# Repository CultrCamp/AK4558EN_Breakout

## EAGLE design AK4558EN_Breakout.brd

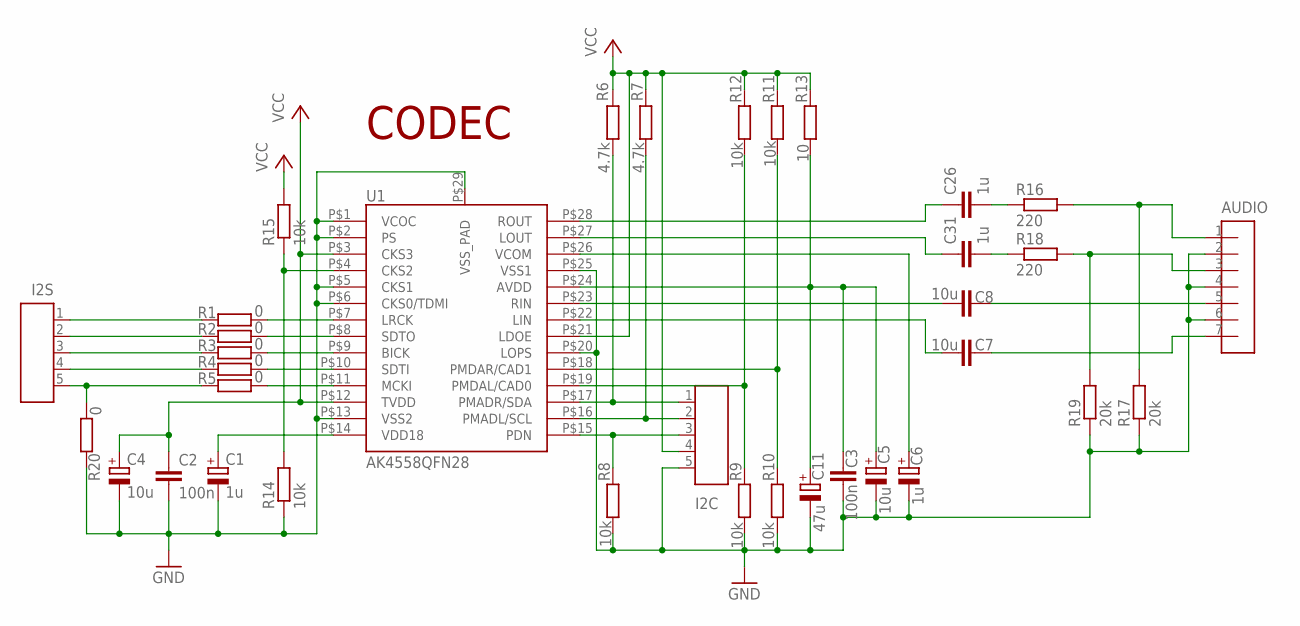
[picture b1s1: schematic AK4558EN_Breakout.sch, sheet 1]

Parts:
AUDIO: PH_ST_7; HDRV7W64P254_1X7_1016X508X838B
C1, C6: 1u; SMC_A
C2, C3: 100n; C0603
C4, C5: 10u; SMC_B
C7, C8: 10u; C0603
C11: 47u; SMC_C
C26, C31: 1u; C0603
I2C, I2S: PH_ST_5; HDRV5W64P254_1X5_1016X508X838B
R1, R2, R3, R4, R5, R20: 0; R0603
R6, R7: 4.7k; R0603
R8, R9, R10, R11, R12, R14, R15: 10k; R0603
R13: 10; R0603
R16, R18: 220; R0603
R17, R19: 20k; R0603
U1: AK4558QFN28; QFN28_5X5

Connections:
CKS2: R14.2, R15.1, U1.P$4 (CKS2)
CODEC_AVDD: C3.1, C5.+, C11.+, R13.1, U1.P$24 (AVDD)
GND: AUDIO.2, AUDIO.4, AUDIO.6, C1.-, C2.2, C3.2, C4.-, C5.-, C6.-, C11.-, I2C.5, R8.1, R9.1, R10.1, R14.1, R17.1, R19.1, R20.1, U1.P$1 (VCOC), U1.P$2 (PS), U1.P$5 (CKS1), U1.P$6 (CKS0/TDMI), U1.P$13 (VSS2), U1.P$20 (LOPS), U1.P$25 (VSS1), U1.P$29 (VSS_PAD)
LIN: AUDIO.7, C7.1
LOUT: AUDIO.3, R18.2, R19.2
MCLK: I2S.5, R5.1, R20.2
unnamed: I2S.4, R4.1
unnamed: C7.2, U1.P$22 (LIN)
unnamed: C26.2, R16.1
unnamed: C6.+, U1.P$26 (VCOM)
unnamed: R5.2, U1.P$11 (MCKI)
unnamed: C8.2, U1.P$23 (RIN)
unnamed: C31.1, U1.P$27 (LOUT)
unnamed: C31.2, R18.1
unnamed: C26.1, U1.P$28 (ROUT)
unnamed: R10.2, R11.1, U1.P$18 (PMDAR/CAD1)
unnamed: R9.2, R12.1, U1.P$19 (PMDAL/CAD0)
unnamed: I2S.3, R3.1
unnamed: I2S.2, R2.1
unnamed: I2S.1, R1.1
unnamed: C1.+, U1.P$14 (VDD18)
unnamed: R1.2, U1.P$7 (LRCK)
unnamed: R2.2, U1.P$8 (SDTO)
unnamed: R3.2, U1.P$9 (BICK)
unnamed: R4.2, U1.P$10 (SDTI)
PDN: I2C.3, R8.2, U1.P$15 (PDN)
RIN: AUDIO.5, C8.1
ROUT: AUDIO.1, R16.2, R17.2
SCL: I2C.2, R7.1, U1.P$16 (PMADL/SCL)
SDA: I2C.1, R6.1, U1.P$17 (PMADR/SDA)
VCC: C2.1, C4.+, I2C.4, R6.2, R7.2, R11.2, R12.2, R13.2, R15.2, U1.P$3 (CKS3), U1.P$12 (TVDD), U1.P$21 (LDOE)

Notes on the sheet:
CODEC

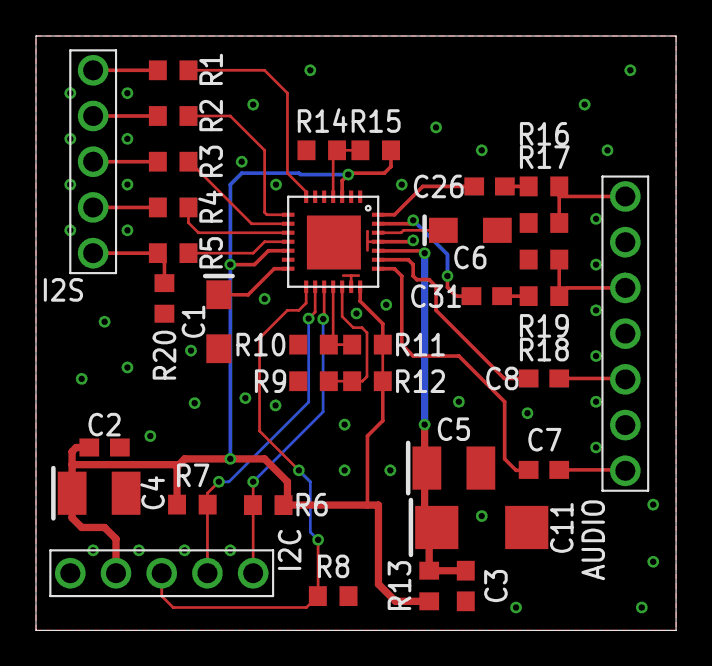
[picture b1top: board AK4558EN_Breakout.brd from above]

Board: 2 copper layers, 35.6 x 33.0 mm, 35 parts (0 on the bottom side), 31 nets.

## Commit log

2020-05-25 update file name
2020-05-25 update schematic and add gerber

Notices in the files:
AK4558EN_Breakout.brd:
Copyright(C) Cultr.camp
